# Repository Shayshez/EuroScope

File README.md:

# EuroScope MKII - DSO150 Eurorack Conversion Kit

[DSO 150](https://www.banggood.com/Orignal-JYE-Tech-DS0150-15001K-DSO-SHELL-DIY-Digital-Oscilloscope-Kit-With-Housing-p-1093865.html?p=PN14171629793201505V&cur_warehouse=CN) Is a cheap mini oscilloscope from JYE TECH.

This conversion kit lets you the ability to convert it to Eruorack module and contains two parts:

* 14 Hp Panel
* Conversion Board
* Optional: [Expander 2Hp PCB+Panel](https://pushermanproductions.com/product/plum-audio-dso150-mk2-oscilloscope-expander-2hp-pcb-panel/) - Provides 3 additional digital inputs (Will work only with [Open DSO 150](https://github.com/michar71/Open-DSO-150) Firmware), OK Botton trigger input and Trigger led.

This is an easy DIY project, just follow the [Build guide](EuroScope_mk2_v2.2-Build_Guide.pdf) (PDF File) I'll recommend to download it to your computer.
(You can find the BOM in the build guide).

* Assemblong Videos Playlist: https://www.youtube.com/watch?v=Akz4jSZyOQc&list=PL2KBIbSMnGOh_Mu7Z_c3bYFIhDCGHZpcL

___________________________________________________
## Alternative Firmware:
There is alternative firmware to DSO150 that add lots of new features, more info at:
[Open DSO 150](https://github.com/michar71/Open-DSO-150)
___________________________________________________
## Which is the right DSO150 DIY Kit?
I checked few sources for the DSO150 kits, only the ones that come from [Banggood](https://www.banggood.com/Orignal-JYE-Tech-DS0150-15001K-DSO-SHELL-DIY-Digital-Oscilloscope-Kit-With-Housing-p-1093865.html?p=PN14171629793201505V&cur_warehouse=CN) was original 2017 version.

Other versions was less accurate and with a lots of ground noises.
If you’re not buying the banggood version you need to find 2017 version and pay attention to (see picture):
1. Trimmers location.
2. Cut in the main PCB for trimmers access.
3. Only 3 electrolytic capacitors in the analog board (not 5).
4. Sticker with Barcode and Serial Number.
5. Silk screen that says it’s 2017 version...

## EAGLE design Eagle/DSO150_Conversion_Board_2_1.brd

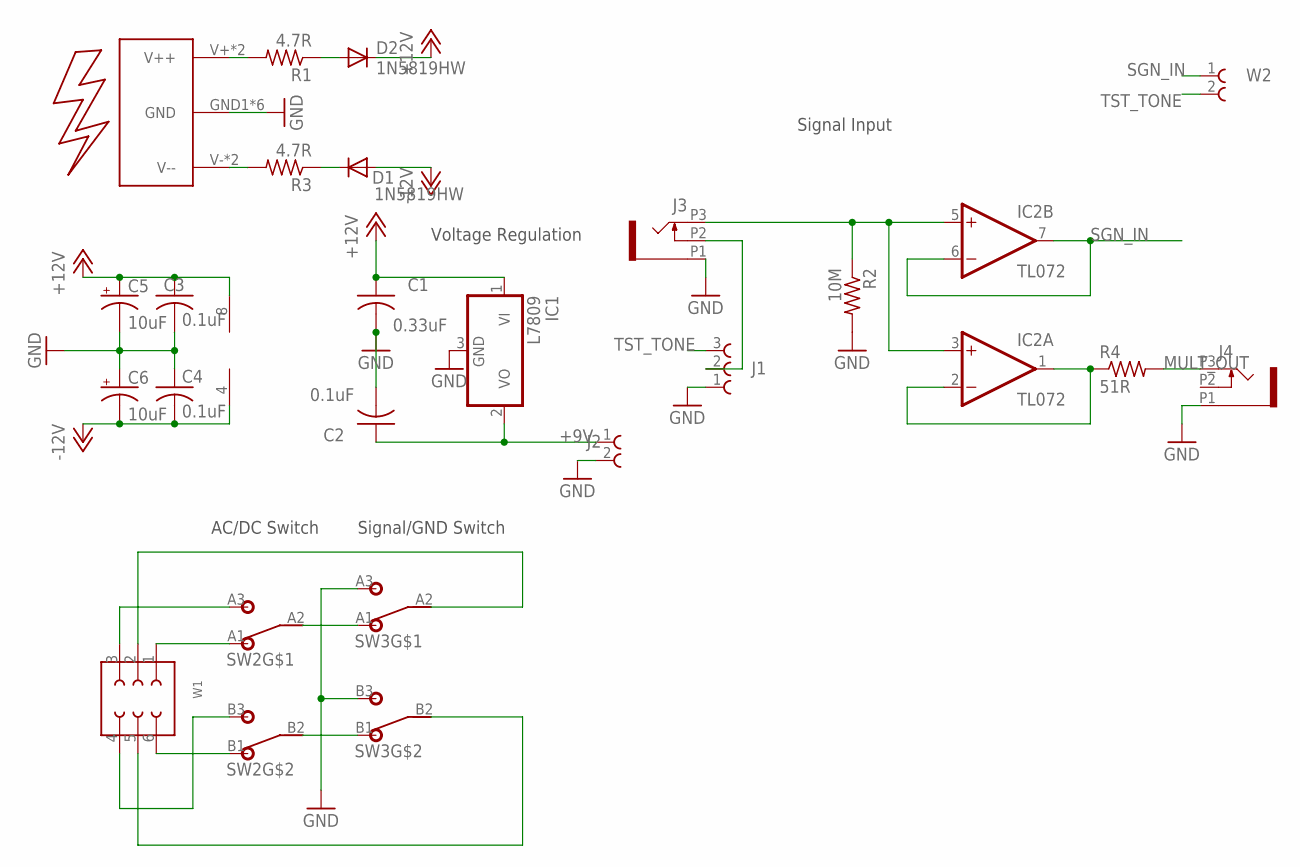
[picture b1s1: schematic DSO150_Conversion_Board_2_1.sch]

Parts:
C1: 0.33uF; C0805
C2, C3, C4: 0.1uF; C0805
C5, C6: 10uF; PANASONIC_B
D1, D2: 1N5819HW; DIODE_SOD123
IC1: L7809; TO252
IC2: TL072; SO08
J1: 61300311121
J2: 61300211121
J3, J4: OG-PJ301_PJ301_THONKICONN7; OG-PJ301_WQP_PJ_301M7
R1, R3: 4.7R; R1206
R2: 10M; R0805
R4: 51R; R0805
SW2, SW3: SUBDPDT; SUBMINIDPDT
U$2: EURO_POWER2
W1: 61300621121
W2: 61300211121

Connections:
+9V: C2.1, IC1.2 (VO), J2.1
+12V: C1.1, C3.1, C5.+, D2.C, IC1.1 (VI), IC2.8 (V+)
-12V: C4.2, C6.-, D1.A, IC2.4 (V-)
GND: C1.2, C2.2, C3.2, C4.1, C5.-, C6.+, IC1.3 (GND), J1.1 (3), J2.2, J3.P1 (1), J4.P1 (1), R2.2, SW3.A3 (3), SW3.B3 (3), U$2.GND1 (GND), U$2.GND2 (GND), U$2.GND3 (GND), U$2.GND4 (GND), U$2.GND5 (GND), U$2.GND6 (GND)
MULT_OUT: IC2.1 (OUT), IC2.2 (-IN), R4.1
unnamed: J1.2, J3.P2 (2)
unnamed: R3.2, U$2.V- (V--), U$2.V--
unnamed: D1.C, R3.1
unnamed: R1.2, U$2.V+ (V++), U$2.V++
unnamed: IC2.3 (+IN), IC2.5 (+IN), J3.P3 (3), R2.1
unnamed: SW2.A1 (1), W1.1
unnamed: SW2.B1 (1), W1.6
unnamed: SW2.B2 (2), SW3.B1 (1)
unnamed: SW2.A2 (2), SW3.A1 (1)
unnamed: J4.P3 (3), R4.2
unnamed: SW2.A3 (3), W1.3
unnamed: SW2.B3 (3), W1.4
unnamed: SW3.A2 (2), W1.2
unnamed: SW3.B2 (2), W1.5
unnamed: D2.A, R1.1
SGN_IN: IC2.6 (-IN), IC2.7 (OUT), W2.1
TST_TONE: J1.3 (1), W2.2

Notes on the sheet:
Voltage Regulation
AC/DC Switch
Signal/GND Switch
Signal Input

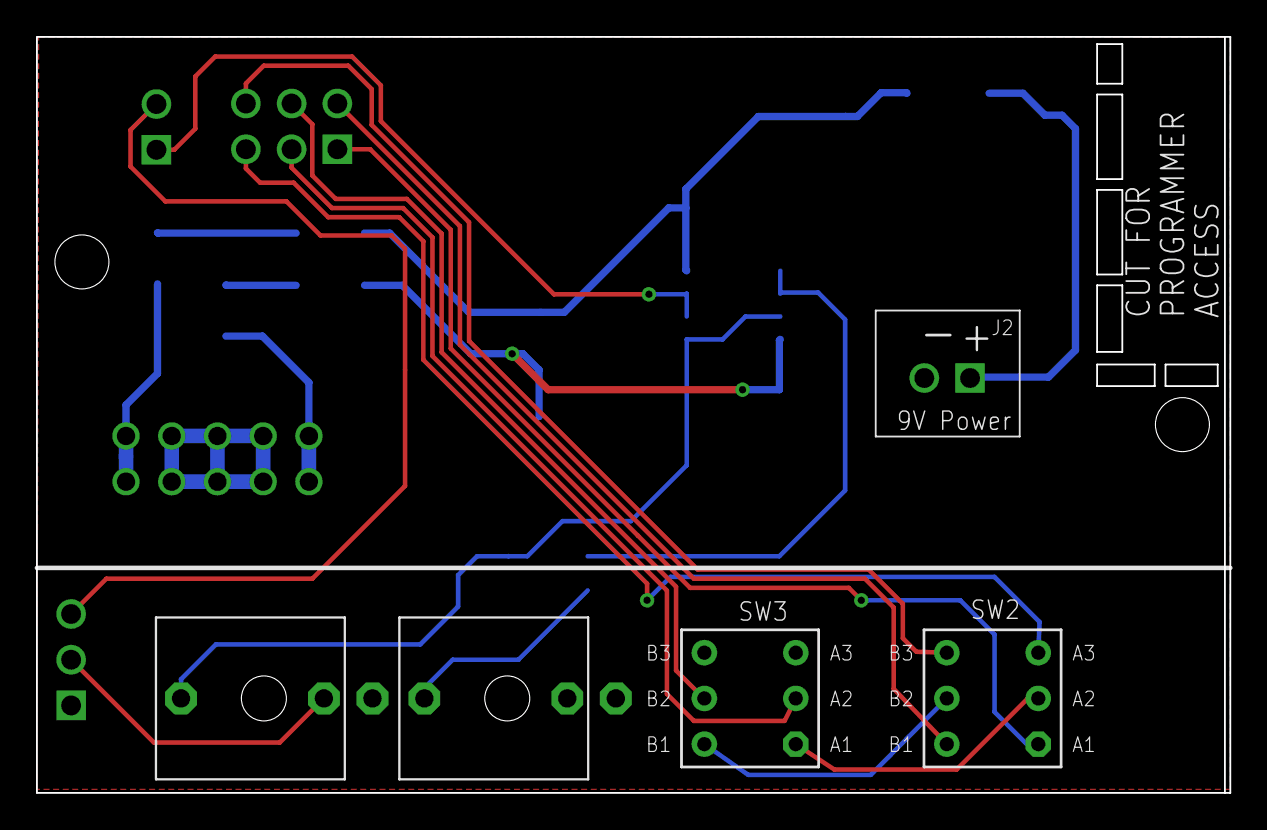
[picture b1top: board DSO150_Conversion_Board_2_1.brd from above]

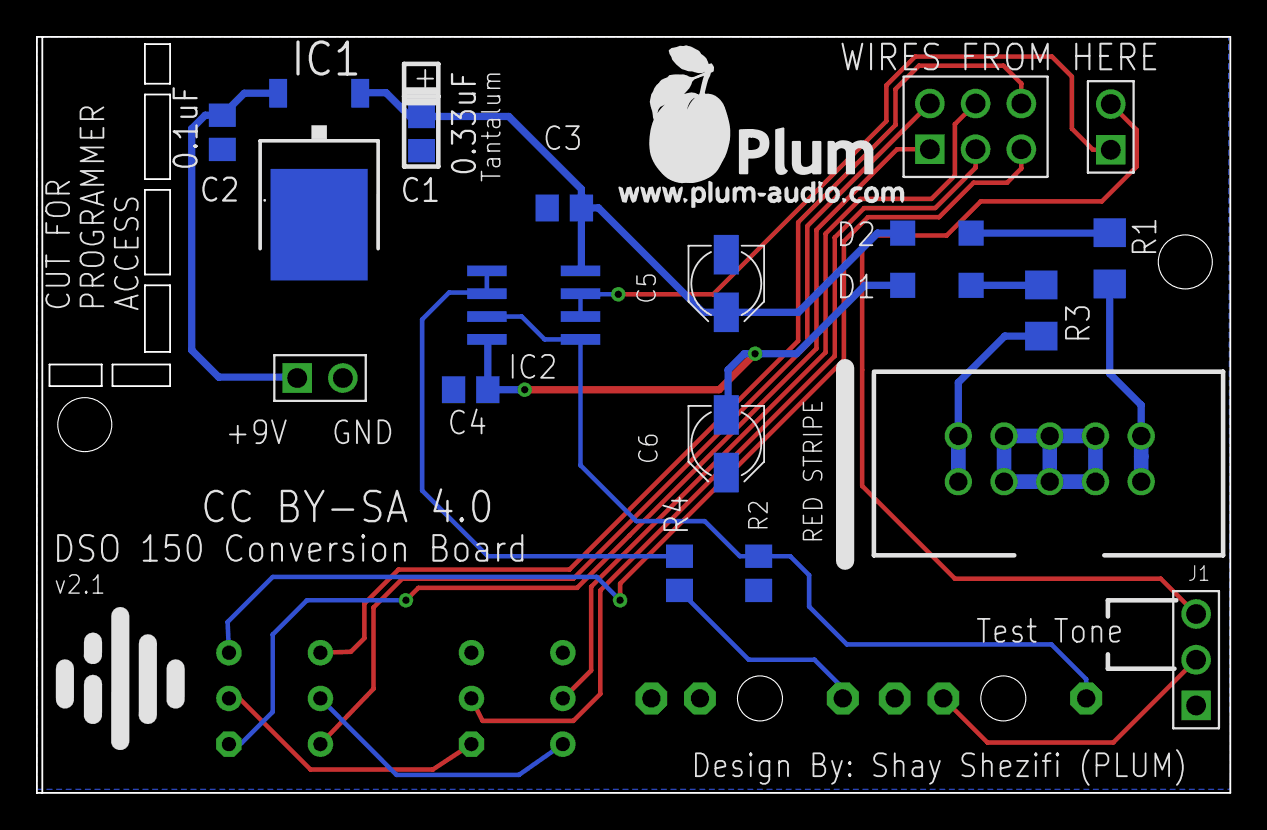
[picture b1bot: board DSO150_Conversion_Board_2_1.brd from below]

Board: 2 copper layers, 66.3 x 42.0 mm, 23 parts (19 on the bottom side), 22 nets.

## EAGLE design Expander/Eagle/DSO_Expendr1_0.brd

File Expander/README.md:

# Expander For EuroScope

Adds additional Buffered inputs:
- 3 Digital Inputs D1, D2, D3 ([Open DSO 150](https://github.com/michar71/Open-DSO-150) Firmware is required).
- OK button trigger input.
- Also, brings the DSO150 Trigger led indicator to front.

### Expander BOM:

|Q|Part|Value|Reference|
|-|----|-----|---------|
|1|Assembled EuroScope|Expander will work with all versions|[Pusherman](https://pushermanproductions.com/product/dso150-mk2-oscilloscope-eurorack-conversion-kit-14hp-pcb-panel/)|
|1|Expander PCB&Panel||[Pusherman](https://pushermanproductions.com/product/plum-audio-dso150-mk2-oscilloscope-expander-2hp-pcb-panel/)|
|4|Resistor 0603|100k|R1, R2, R3, R4|
|1|Resistor 0603|1K|R5 (For Led Brightness)|
|4|NPN Transistor| MMBT3904|T1, T2, T3, T4|
|1|LED 1206|Any colour you like...|LED1|
|4|Jack PJ398SM|"Thonkiconn"|J2, J3, J4, J5|
|1|Male Pin headers 2.54| 1 row of 7 Pins| J1|

**To connect between Boards:**

|Q|Part|Value|Reference|
|-|----|-----|---------|
|1|Male Pin headers 2.54| 1 row of 8 Pins|**DSO150 Main Board:** J9 (For Connection with Expander)|
|1|Male Pin headers 2.54| 1 row of 4 Pins|**DSO150 Main Board:** J3 (SWD - To Update the Firmware)
|7|Female to Female Jumper Wire|To connect between Boards||
|1|Male to Male Jumper Wire|To connect between Boards|| 

**How To Build?**
1. Build the Expander... Solder all components in place and assemble the panel.
2. Connect the Expander:

|Expander J1|DSO 150|
|-----------|-------|
|3.3V|3.3V @J9|
|PB13|PB13 @J9|
|PB14|PB14 @J9|
|PB15|PB15 @J9|
|GND|GND @J9|

Cut Male to Male Jumper wire into two parts and solder to DSO150:

|Expander J1|DSO 150|
|-----------|-------|
|OK|Top Right Pin of OK Button|
|LED|Remove R14 and solder this wire to top pad of R14|

___________________________________________________________________________
# Firmware Update:

I'm using ST-LINK V2 with ST-LINK Utility software on Windows Environment.
You can find hex file in this repo ([here](Firmware%20-%20Open%20DSO150)) 

Connect the programer to DSO150:

|ST-LINK JTAG Port|DSO 150 SWD Port|
|-----------------|-------|
|Pin 1|3.3V @J3|
|Pin 3|GND @J3|
|Pin 7|DIO @J3|
|Pin 9|CLK @J3|

***For next steps you need to connect your EuroScope to power source.**

**With ST-LINK Utility Software:**
1. Go to Target->Settings and choose SWD Port, Frequency = 4.0 MHz, After you click "OK" the programer should connect to DSO150 automatically.
2. Go to Target->Program & Verify, Browse and select new firmware [hex file](Firmware%20-%20Open%20DSO150) and hit Start
3. After the Flash process finished, restart EuroScope and hold "OK" button during boot up.

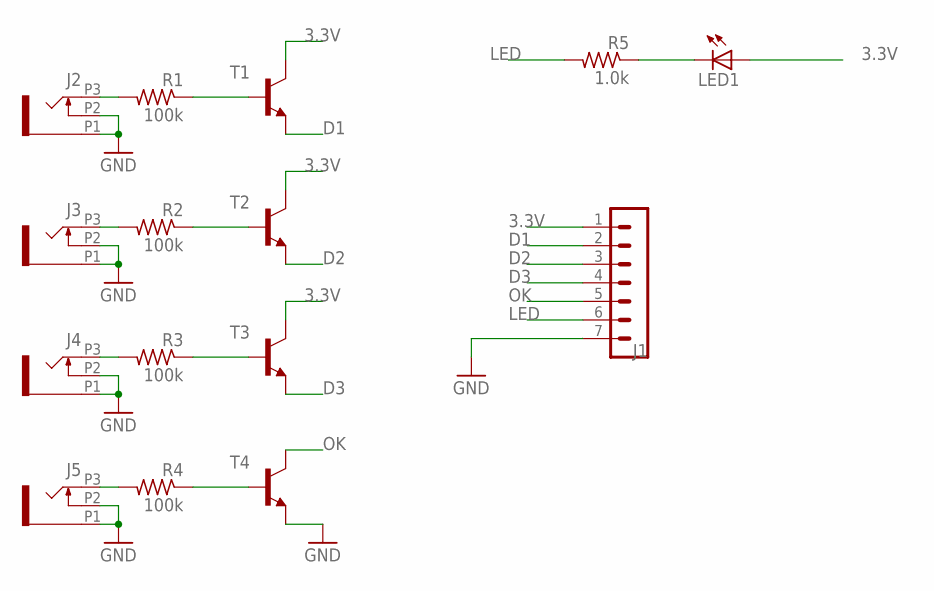
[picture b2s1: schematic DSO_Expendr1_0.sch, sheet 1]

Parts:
J1: MA07-1
J2, J3, J4, J5: OG-PJ301_PJ301_THONKICONN; OG-PJ301_WQP_PJ_301M6_NO_HOLE
LED1: LED_E; LED_1206
R1, R2, R3, R4: 100k; R0805
R5: 1.0k; R0805
T1, T2, T3, T4: MMBT3904LT1-NPN-SOT23-BEC; SOT23-BEC

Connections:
3.3V: J1.1, LED1.A, T1.C, T2.C, T3.C
D1: J1.2, T1.E
D2: J1.3, T2.E
D3: J1.4, T3.E
GND: J1.7, J2.P1 (1), J2.P2 (2), J3.P1 (1), J3.P2 (2), J4.P1 (1), J4.P2 (2), J5.P1 (1), J5.P2 (2), T4.E
LED: J1.6, R5.2
unnamed: J2.P3 (3), R1.2
unnamed: R1.1, T1.B
unnamed: J3.P3 (3), R2.2
unnamed: R2.1, T2.B
unnamed: J4.P3 (3), R3.2
unnamed: R3.1, T3.B
unnamed: J5.P3 (3), R4.2
unnamed: R4.1, T4.B
unnamed: LED1.C, R5.1
OK: J1.5, T4.C

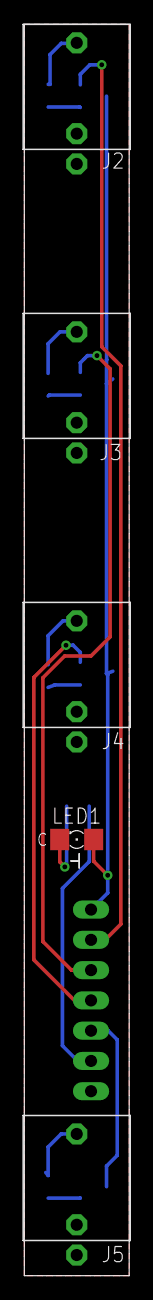
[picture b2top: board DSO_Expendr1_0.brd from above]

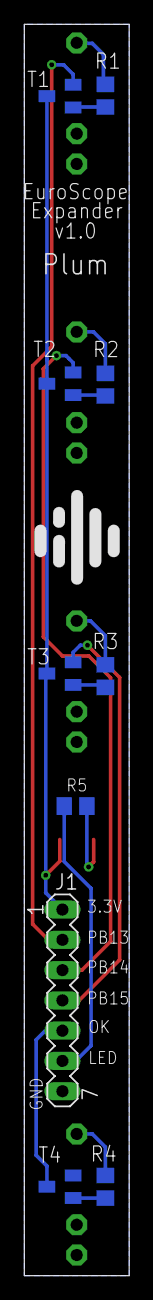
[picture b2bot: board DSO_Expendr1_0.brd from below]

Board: 2 copper layers, 8.8 x 105.0 mm, 15 parts (10 on the bottom side), 16 nets.

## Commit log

2019-02-11 EuroScope v1.0 Backup
2019-10-03 Updated BOM for v2.2
2019-10-03 Updated BOM v2.2
2020-05-04 Add spreadsheet for the BOM
    A spreadsheet is much easier to use than the PDF for tracking what you've bought and or installed :)
2021-01-01 Update README.md
    Corrected typos

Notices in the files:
Eagle/DSO150_Conversion_Board_2_1.brd:
CC BY-SA 4.0
parts and their libraries:
Wurth_Elektronik_Electromechanic_Board_t: Copyright: Würth Elektronik
